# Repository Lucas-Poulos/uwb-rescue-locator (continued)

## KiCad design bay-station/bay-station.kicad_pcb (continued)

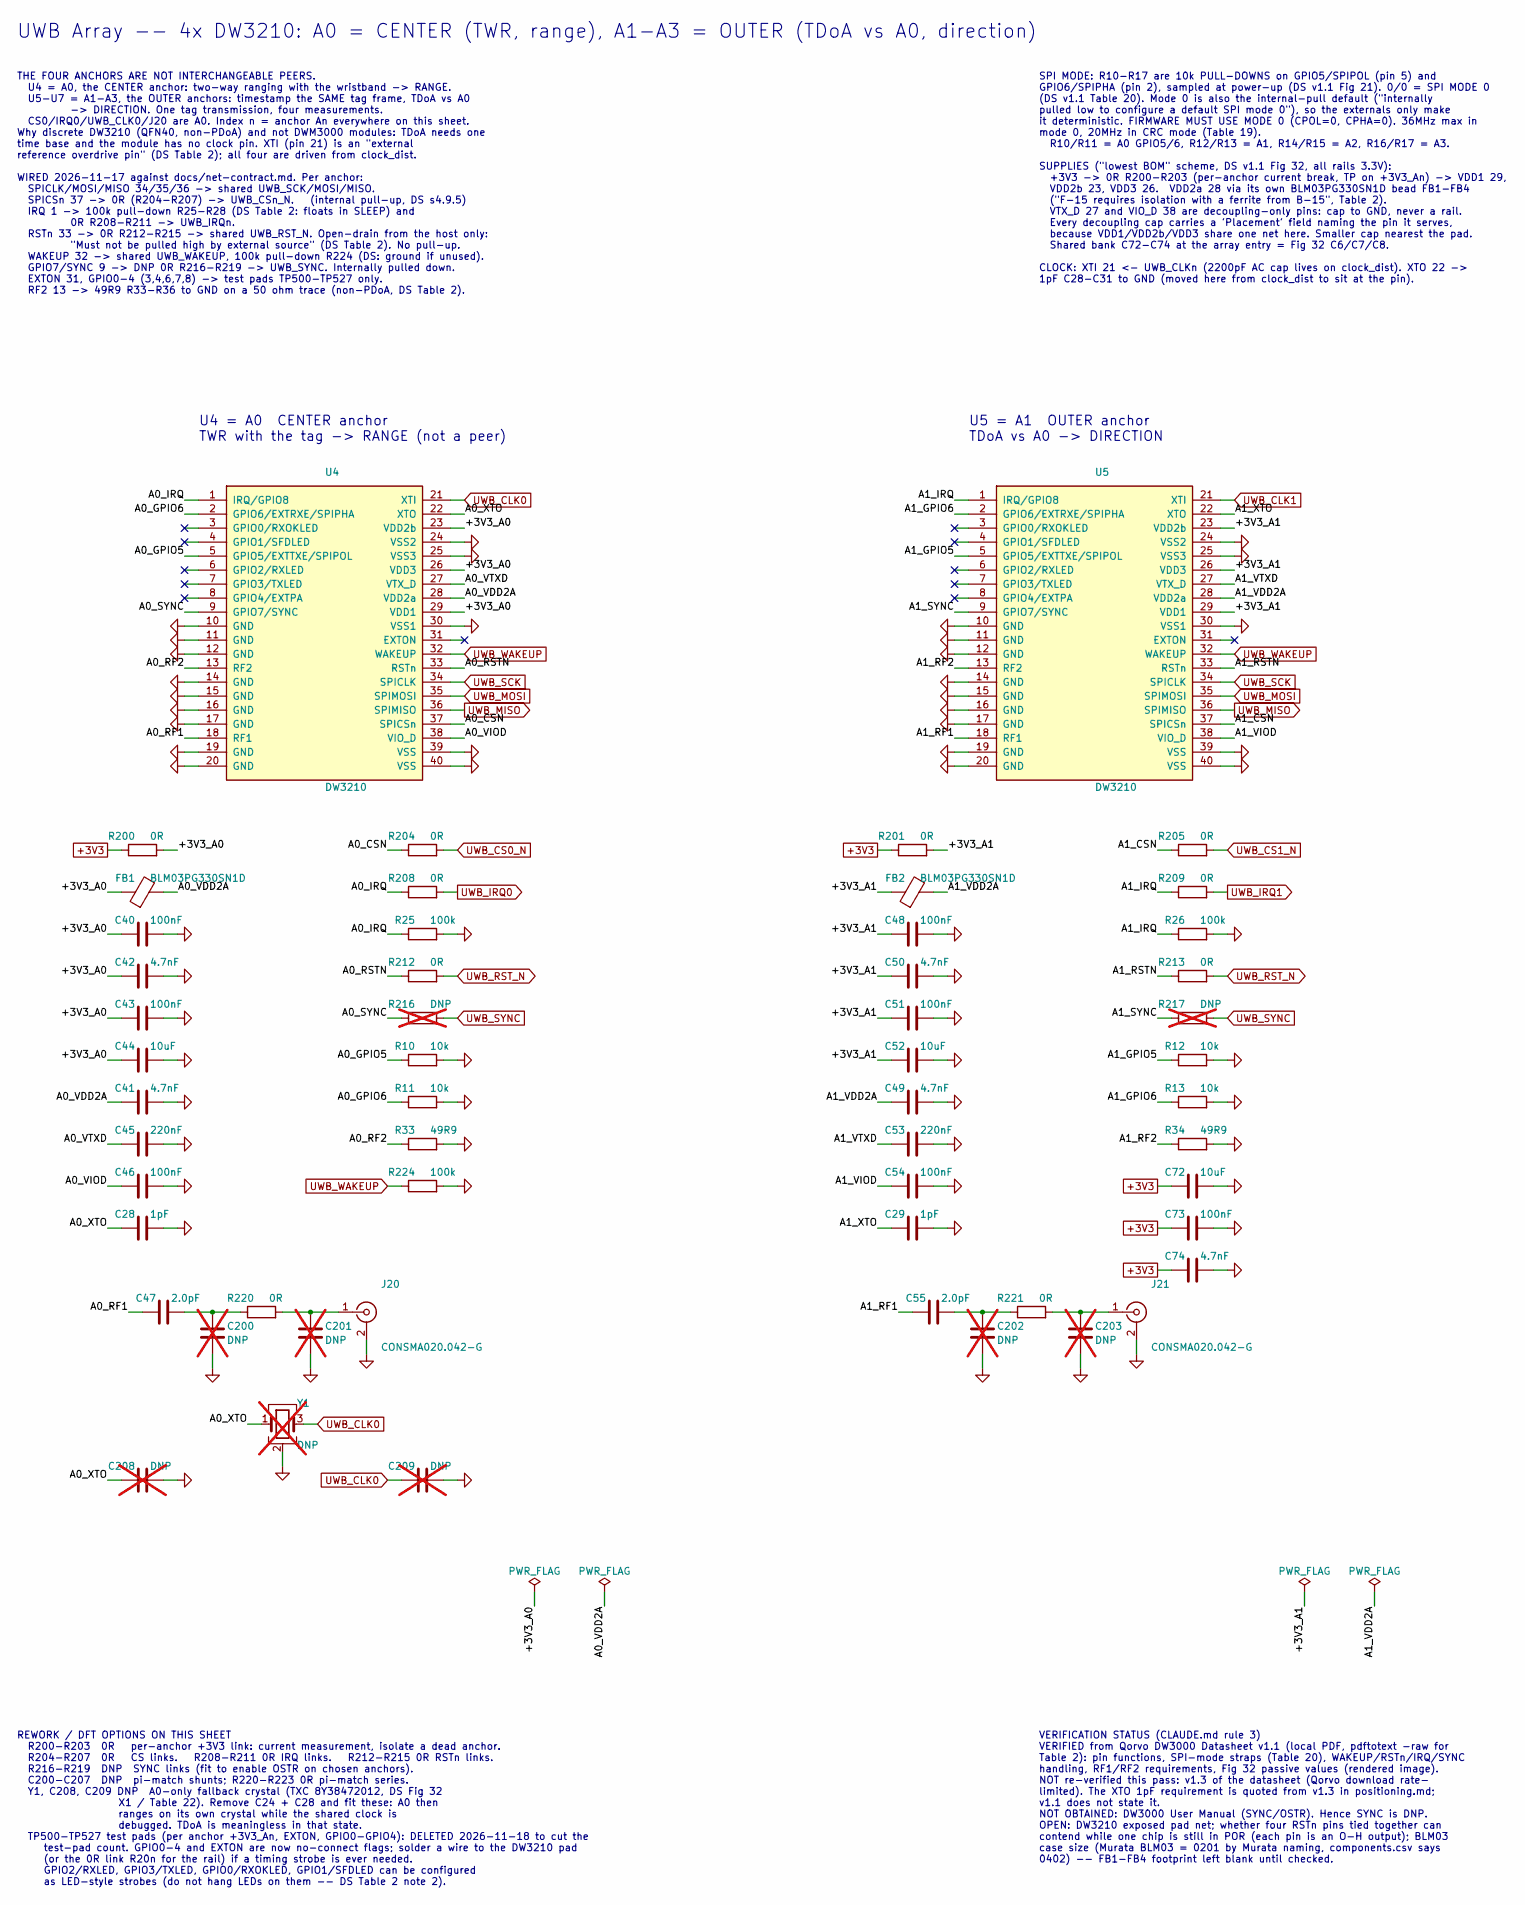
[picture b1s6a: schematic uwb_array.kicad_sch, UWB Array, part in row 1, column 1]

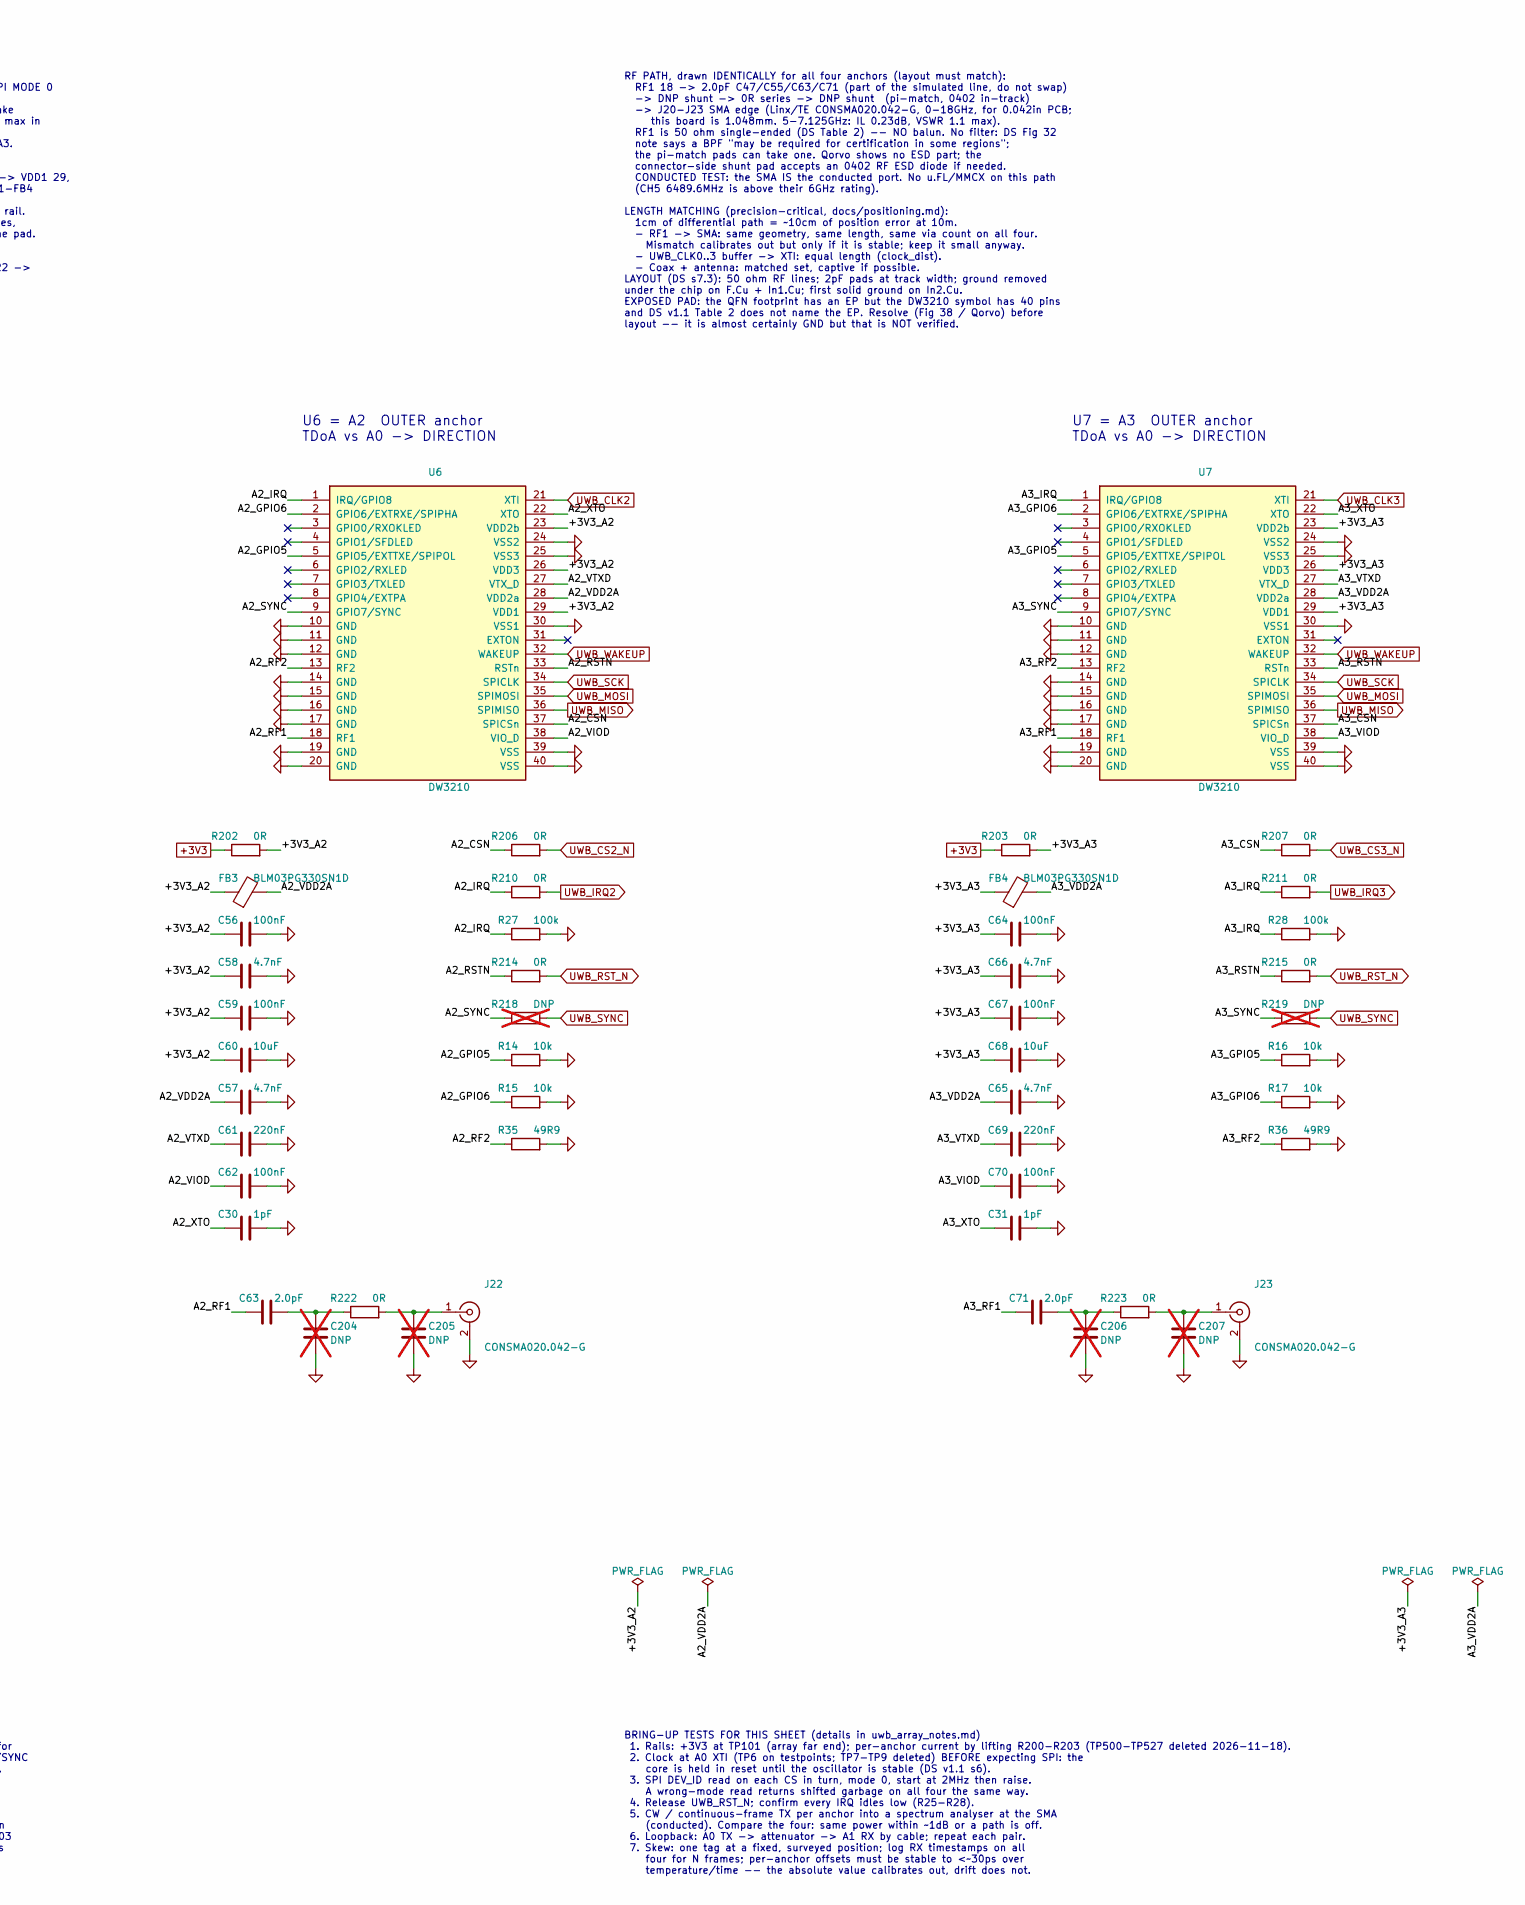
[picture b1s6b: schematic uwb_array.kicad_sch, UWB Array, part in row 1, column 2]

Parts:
C28, C29, C30, C31: 1pF; C_0402_1005Metric
C40, C43, C46, C48, C51, C54, C56, C59, C62, C64, C67, C70, C73: 100nF; C_0603_1608Metric
C41, C42, C49, C50, C57, C58, C65, C66, C74: 4.7nF; C_0603_1608Metric
C44, C52, C60, C68, C72: 10uF; C_0603_1608Metric
C45, C53, C61, C69: 220nF; C_0603_1608Metric
C47, C55, C63, C71: 2.0pF; C_0402_1005Metric
C200, C201, C202, C203, C204, C205, C206, C207, C208, C209: DNP; C_0402_1005Metric; not fitted
FB1, FB2, FB3, FB4: BLM03PG330SN1D; L_0201_0603Metric
J20, J21, J22, J23: CONSMA020.042-G; SMA_Linx_CONSMA020.042-G_EdgeMount_PLACEHOLDER
R10, R11, R12, R13, R14, R15, R16, R17: 10k; R_0603_1608Metric
R25, R26, R27, R28, R224: 100k; R_0603_1608Metric
R33, R34, R35, R36: 49R9; R_0402_1005Metric
R200, R201, R202, R203, R204, R205, R206, R207, R208, R209, R210, R211, R212, R213, R214, R215: 0R; R_0603_1608Metric
R216, R217, R218, R219: DNP; R_0603_1608Metric; not fitted
R220, R221, R222, R223: 0R; R_0402_1005Metric
U4, U5, U6, U7: DW3210; Qorvo_DW3210_QFN-40_5x5mm_P0.4mm_NoEP_PLACEHOLDER
Y1: DNP; Crystal_SMD_2016-4Pin_2.0x1.6mm; MPN 8Y38472012; not fitted

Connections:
+3V3: C72.1, C73.1, C74.1, R200.1, R201.1, R202.1, R203.1; also elsewhere on the board
/UWB Array/+3V3_A0: C40.1, C42.1, C43.1, C44.1, FB1.1, R200.2, U4.23 (VDD2b), U4.26 (VDD3), U4.29 (VDD1)
/UWB Array/+3V3_A1: C48.1, C50.1, C51.1, C52.1, FB2.1, R201.2, U5.23 (VDD2b), U5.26 (VDD3), U5.29 (VDD1)
/UWB Array/+3V3_A2: C56.1, C58.1, C59.1, C60.1, FB3.1, R202.2, U6.23 (VDD2b), U6.26 (VDD3), U6.29 (VDD1)
/UWB Array/+3V3_A3: C64.1, C66.1, C67.1, C68.1, FB4.1, R203.2, U7.23 (VDD2b), U7.26 (VDD3), U7.29 (VDD1)
/UWB Array/A0_CSN: R204.1, U4.37 (SPICSn)
/UWB Array/A0_GPIO5: R10.1, U4.5 (GPIO5/EXTTXE/SPIPOL)
/UWB Array/A0_GPIO6: R11.1, U4.2 (GPIO6/EXTRXE/SPIPHA)
/UWB Array/A0_IRQ: R25.1, R208.1, U4.1 (IRQ/GPIO8)
/UWB Array/A0_RF1: C47.1, U4.18 (RF1)
/UWB Array/A0_RF2: R33.1, U4.13 (RF2)
/UWB Array/A0_RSTN: R212.1, U4.33 (RSTn)
/UWB Array/A0_SYNC: R216.1, U4.9 (GPIO7/SYNC)
/UWB Array/A0_VDD2A: C41.1, FB1.2, U4.28 (VDD2a)
/UWB Array/A0_VIOD: C46.1, U4.38 (VIO_D)
/UWB Array/A0_VTXD: C45.1, U4.27 (VTX_D)
/UWB Array/A0_XTO: C28.1, C208.1, U4.22 (XTO), Y1.1
/UWB Array/A1_CSN: R205.1, U5.37 (SPICSn)
/UWB Array/A1_GPIO5: R12.1, U5.5 (GPIO5/EXTTXE/SPIPOL)
/UWB Array/A1_GPIO6: R13.1, U5.2 (GPIO6/EXTRXE/SPIPHA)
/UWB Array/A1_IRQ: R26.1, R209.1, U5.1 (IRQ/GPIO8)
/UWB Array/A1_RF1: C55.1, U5.18 (RF1)
/UWB Array/A1_RF2: R34.1, U5.13 (RF2)
/UWB Array/A1_RSTN: R213.1, U5.33 (RSTn)
/UWB Array/A1_SYNC: R217.1, U5.9 (GPIO7/SYNC)
/UWB Array/A1_VDD2A: C49.1, FB2.2, U5.28 (VDD2a)
/UWB Array/A1_VIOD: C54.1, U5.38 (VIO_D)
/UWB Array/A1_VTXD: C53.1, U5.27 (VTX_D)
/UWB Array/A1_XTO: C29.1, U5.22 (XTO)
/UWB Array/A2_CSN: R206.1, U6.37 (SPICSn)
/UWB Array/A2_GPIO5: R14.1, U6.5 (GPIO5/EXTTXE/SPIPOL)
/UWB Array/A2_GPIO6: R15.1, U6.2 (GPIO6/EXTRXE/SPIPHA)
/UWB Array/A2_IRQ: R27.1, R210.1, U6.1 (IRQ/GPIO8)
/UWB Array/A2_RF1: C63.1, U6.18 (RF1)
/UWB Array/A2_RF2: R35.1, U6.13 (RF2)
/UWB Array/A2_RSTN: R214.1, U6.33 (RSTn)
/UWB Array/A2_SYNC: R218.1, U6.9 (GPIO7/SYNC)
/UWB Array/A2_VDD2A: C57.1, FB3.2, U6.28 (VDD2a)
/UWB Array/A2_VIOD: C62.1, U6.38 (VIO_D)
/UWB Array/A2_VTXD: C61.1, U6.27 (VTX_D)
/UWB Array/A2_XTO: C30.1, U6.22 (XTO)
/UWB Array/A3_CSN: R207.1, U7.37 (SPICSn)
/UWB Array/A3_GPIO5: R16.1, U7.5 (GPIO5/EXTTXE/SPIPOL)
/UWB Array/A3_GPIO6: R17.1, U7.2 (GPIO6/EXTRXE/SPIPHA)
/UWB Array/A3_IRQ: R28.1, R211.1, U7.1 (IRQ/GPIO8)
/UWB Array/A3_RF1: C71.1, U7.18 (RF1)
/UWB Array/A3_RF2: R36.1, U7.13 (RF2)
/UWB Array/A3_RSTN: R215.1, U7.33 (RSTn)
/UWB Array/A3_SYNC: R219.1, U7.9 (GPIO7/SYNC)
/UWB Array/A3_VDD2A: C65.1, FB4.2, U7.28 (VDD2a)
/UWB Array/A3_VIOD: C70.1, U7.38 (VIO_D)
/UWB Array/A3_VTXD: C69.1, U7.27 (VTX_D)
/UWB Array/A3_XTO: C31.1, U7.22 (XTO)
GND: C28.2, C29.2, C30.2, C31.2, C40.2, C41.2, C42.2, C43.2, C44.2, C45.2, C46.2, C48.2, C49.2, C50.2, C51.2, C52.2, C53.2, C54.2, C56.2, C57.2, C58.2, C59.2, C60.2, C61.2, C62.2, C64.2, C65.2, C66.2, C67.2, C68.2, C69.2, C70.2, C72.2, C73.2, C74.2, C200.2, C201.2, C202.2, C203.2, C204.2, C205.2, C206.2, C207.2, C208.2, C209.2, J20.2 (Ext), J21.2 (Ext), J22.2 (Ext), J23.2 (Ext), R10.2, R11.2, R12.2, R13.2, R14.2, R15.2, R16.2, R17.2, R25.2, R26.2, R27.2, R28.2, R33.2, R34.2, R35.2, R36.2, R224.2, U4.10 (GND), U4.11 (GND), U4.12 (GND), U4.14 (GND), U4.15 (GND), U4.16 (GND), U4.17 (GND), U4.19 (GND), U4.20 (GND), U4.24 (VSS2), U4.25 (VSS3), U4.30 (VSS1), U4.39 (VSS), U4.40 (VSS), U5.10 (GND), U5.11 (GND), U5.12 (GND), U5.14 (GND), U5.15 (GND), U5.16 (GND), U5.17 (GND), U5.19 (GND), U5.20 (GND), U5.24 (VSS2), U5.25 (VSS3), U5.30 (VSS1), U5.39 (VSS), U5.40 (VSS), U6.10 (GND), U6.11 (GND), U6.12 (GND), U6.14 (GND), U6.15 (GND), U6.16 (GND), U6.17 (GND), U6.19 (GND), U6.20 (GND), U6.24 (VSS2), U6.25 (VSS3), U6.30 (VSS1), U6.39 (VSS), U6.40 (VSS), U7.10 (GND), U7.11 (GND), U7.12 (GND), U7.14 (GND), U7.15 (GND), U7.16 (GND), U7.17 (GND), U7.19 (GND), U7.20 (GND), U7.24 (VSS2), U7.25 (VSS3), U7.30 (VSS1), U7.39 (VSS), U7.40 (VSS), Y1.2 (G), Y1.4 (G); also elsewhere on the board
unnamed: C47.2, C200.1, R220.1
unnamed: C55.2, C202.1, R221.1
unnamed: C63.2, C204.1, R222.1
unnamed: C71.2, C206.1, R223.1
unnamed: C201.1, J20.1 (In), R220.2
unnamed: C203.1, J21.1 (In), R221.2
unnamed: C205.1, J22.1 (In), R222.2
unnamed: C207.1, J23.1 (In), R223.2
UWB_CLK0: C209.1, U4.21 (XTI), Y1.3; also elsewhere on the board
UWB_CLK1: U5.21 (XTI); also elsewhere on the board
UWB_CLK2: U6.21 (XTI); also elsewhere on the board
UWB_CLK3: U7.21 (XTI); also elsewhere on the board
UWB_CS0_N: R204.2; also elsewhere on the board
UWB_CS1_N: R205.2; also elsewhere on the board
UWB_CS2_N: R206.2; also elsewhere on the board
UWB_CS3_N: R207.2; also elsewhere on the board
UWB_IRQ0: R208.2; also elsewhere on the board
UWB_IRQ1: R209.2; also elsewhere on the board
UWB_IRQ2: R210.2; also elsewhere on the board
UWB_IRQ3: R211.2; also elsewhere on the board
UWB_MISO: U4.36 (SPIMISO), U5.36 (SPIMISO), U6.36 (SPIMISO), U7.36 (SPIMISO); also elsewhere on the board
UWB_MOSI: U4.35 (SPIMOSI), U5.35 (SPIMOSI), U6.35 (SPIMOSI), U7.35 (SPIMOSI); also elsewhere on the board
UWB_RST_N: R212.2, R213.2, R214.2, R215.2; also elsewhere on the board
UWB_SCK: U4.34 (SPICLK), U5.34 (SPICLK), U6.34 (SPICLK), U7.34 (SPICLK); also elsewhere on the board
UWB_SYNC: R216.2, R217.2, R218.2, R219.2; also elsewhere on the board
UWB_WAKEUP: R224.1, U4.32 (WAKEUP), U5.32 (WAKEUP), U6.32 (WAKEUP), U7.32 (WAKEUP); also elsewhere on the board

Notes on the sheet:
VERIFICATION STATUS (CLAUDE.md rule 3) VERIFIED from Qorvo DW3000 Datasheet v1.1 (local PDF, pdftotext -raw for Table 2): pin functions, SPI-mode straps (Table 20), WAKEUP/RSTn/IRQ/SYNC handling, RF1/RF2 requirements, Fig 32 passive values (rendered image). NOT re-verified this pass: v1.3 of the da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
U7 = A3 OUTER anchor TDoA vs A0 -> DIRECTION
U6 = A2 OUTER anchor TDoA vs A0 -> DIRECTION
BRING-UP TESTS FOR THIS SHEET (details in uwb_array_notes.md) 1. Rails: +3V3 at TP101 (array far end); per-anchor current by lifting R200-R203 (TP500-TP527 deleted 2026-11-18). 2. Clock at A0 XTI (TP6 on testpoints; TP7-TP9 deleted) BEFORE expecting SPI: the core is held in reset until the oscillat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
UWB Array -- 4x DW3210: A0 = CENTER (TWR, range), A1-A3 = OUTER (TDoA vs A0, direction)
THE FOUR ANCHORS ARE NOT INTERCHANGEABLE PEERS. U4 = A0, the CENTER anchor: two-way ranging with the wristband -> RANGE. U5-U7 = A1-A3, the OUTER anchors: timestamp the SAME tag frame, TDoA vs A0 -> DIRECTION. One tag transmission, four measurements. CS0/IRQ0/UWB_CLK0/J20 are A0. Index n = anchor A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
SPI MODE: R10-R17 are 10k PULL-DOWNS on GPIO5/SPIPOL (pin 5) and GPIO6/SPIPHA (pin 2), sampled at power-up (DS v1.1 Fig 21). 0/0 = SPI MODE 0 (DS v1.1 Table 20). Mode 0 is also the internal-pull default ("internally pulled low to configure a default SPI mode 0"), so the externals only make it deter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
RF PATH, drawn IDENTICALLY for all four anchors (layout must match): RF1 18 -> 2.0pF C47/C55/C63/C71 (part of the simulated line, do not swap) -> DNP shunt -> 0R series -> DNP shunt (pi-match, 0402 in-track) -> J20-J23 SMA edge (Linx/TE CONSMA020.042-G, 0-18GHz, for 0.042in PCB; this board is 1.048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
U5 = A1 OUTER anchor TDoA vs A0 -> DIRECTION
U4 = A0 CENTER anchor TWR with the tag -> RANGE (not a peer)
REWORK / DFT OPTIONS ON THIS SHEET R200-R203 0R per-anchor +3V3 link: current measurement, isolate a dead anchor. R204-R207 0R CS links. R208-R211 0R IRQ links. R212-R215 0R RSTn links. R216-R219 DNP SYNC links (fit to enable OSTR on chosen anchors). C200-C207 DNP pi-match shunts; R220-R223 0R pi-m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

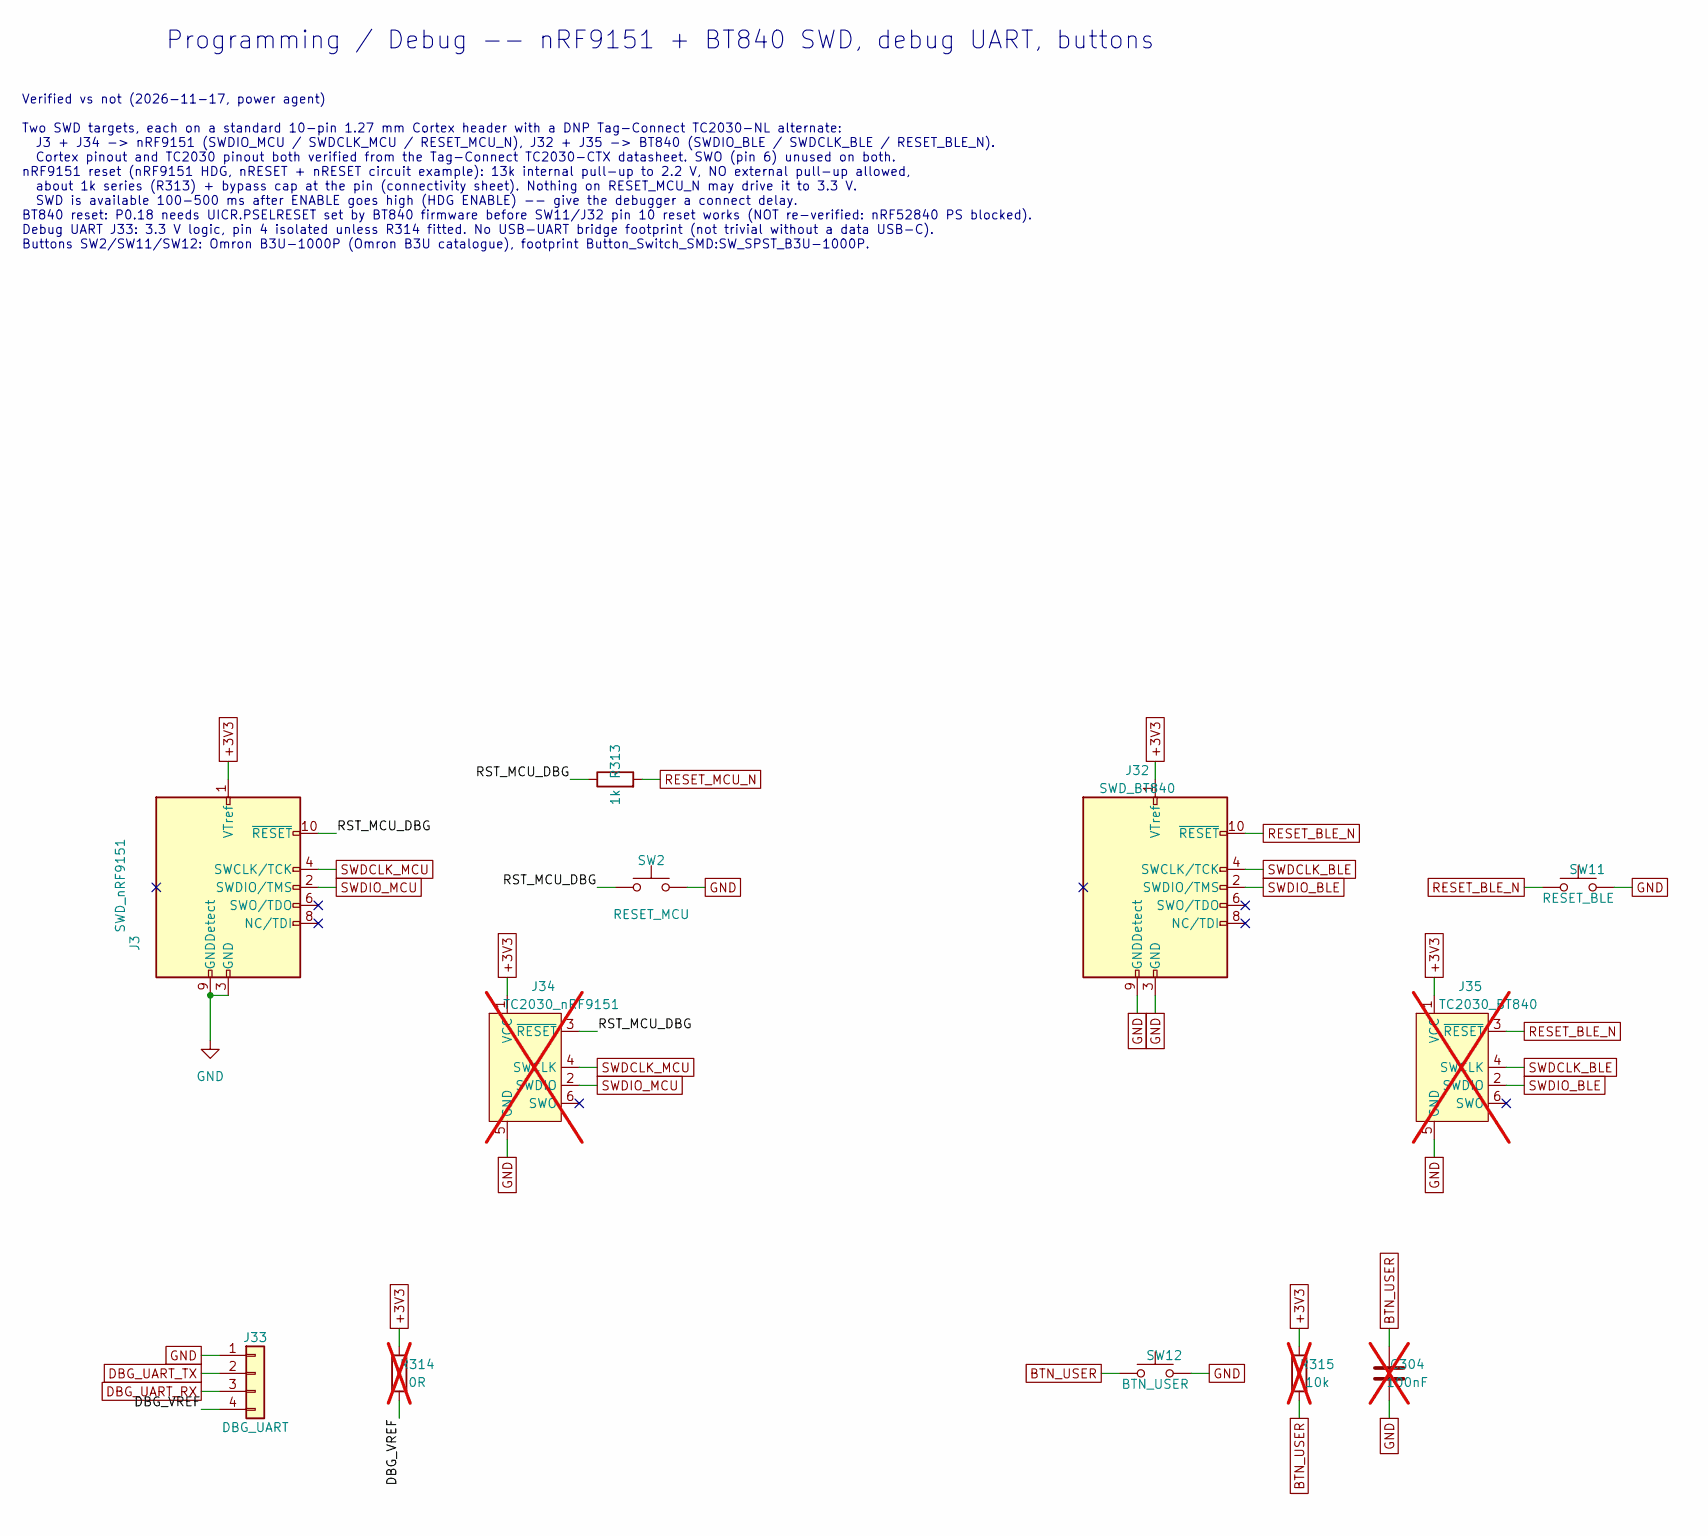
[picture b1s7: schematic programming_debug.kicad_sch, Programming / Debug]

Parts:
C304: 100nF; C_0603_1608Metric; not fitted
J3: SWD_nRF9151; PinHeader_2x05_P1.27mm_Vertical
J32: SWD_BT840; PinHeader_2x05_P1.27mm_Vertical
J33: DBG_UART; PinHeader_1x04_P2.54mm_Vertical
J34: TC2030_nRF9151; Tag-Connect_TC2030-IDC-NL_2x03_P1.27mm_Vertical; not fitted
J35: TC2030_BT840; Tag-Connect_TC2030-IDC-NL_2x03_P1.27mm_Vertical; not fitted
R313: 1k; R_0603_1608Metric
R314: 0R; R_0603_1608Metric; not fitted
R315: 10k; R_0603_1608Metric; not fitted
SW2: RESET_MCU; SW_SPST_B3U-1000P; MPN B3U-1000P
SW11: RESET_BLE; SW_SPST_B3U-1000P; MPN B3U-1000P
SW12: BTN_USER; SW_SPST_B3U-1000P; MPN B3U-1000P

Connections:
+3V3: J3.1 (VTref), J32.1 (VTref), J34.1 (VCC), J35.1 (VCC), R314.1, R315.1; also elsewhere on the board
/Programming / Debug/DBG_VREF: J33.4, R314.2
/Programming / Debug/RST_MCU_DBG: J3.10 (~RESET), J34.3 (~RESET), R313.1, SW2.1
BTN_USER: C304.1, R315.2, SW12.1; also elsewhere on the board
DBG_UART_RX: J33.3; also elsewhere on the board
DBG_UART_TX: J33.2; also elsewhere on the board
GND: C304.2, J3.3 (GND), J3.5 (GND), J3.9 (GNDDetect), J32.3 (GND), J32.5 (GND), J32.9 (GNDDetect), J33.1, J34.5 (GND), J35.5 (GND), SW2.2, SW11.2, SW12.2; also elsewhere on the board
RESET_BLE_N: J32.10 (~RESET), J35.3 (~RESET), SW11.1; also elsewhere on the board
RESET_MCU_N: R313.2; also elsewhere on the board
SWDCLK_BLE: J32.4 (SWCLK/TCK), J35.4 (SWCLK); also elsewhere on the board
SWDCLK_MCU: J3.4 (SWCLK/TCK), J34.4 (SWCLK); also elsewhere on the board
SWDIO_BLE: J32.2 (SWDIO/TMS), J35.2 (SWDIO); also elsewhere on the board
SWDIO_MCU: J3.2 (SWDIO/TMS), J34.2 (SWDIO); also elsewhere on the board

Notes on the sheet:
Verified vs not (2026-11-17, power agent) Two SWD targets, each on a standard 10-pin 1.27 mm Cortex header with a DNP Tag-Connect TC2030-NL alternate: J3 + J34 -> nRF9151 (SWDIO_MCU / SWDCLK_MCU / RESET_MCU_N), J32 + J35 -> BT840 (SWDIO_BLE / SWDCLK_BLE / RESET_BLE_N). Cortex pinout and TC2030 pino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
Programming / Debug -- nRF9151 + BT840 SWD, debug UART, buttons

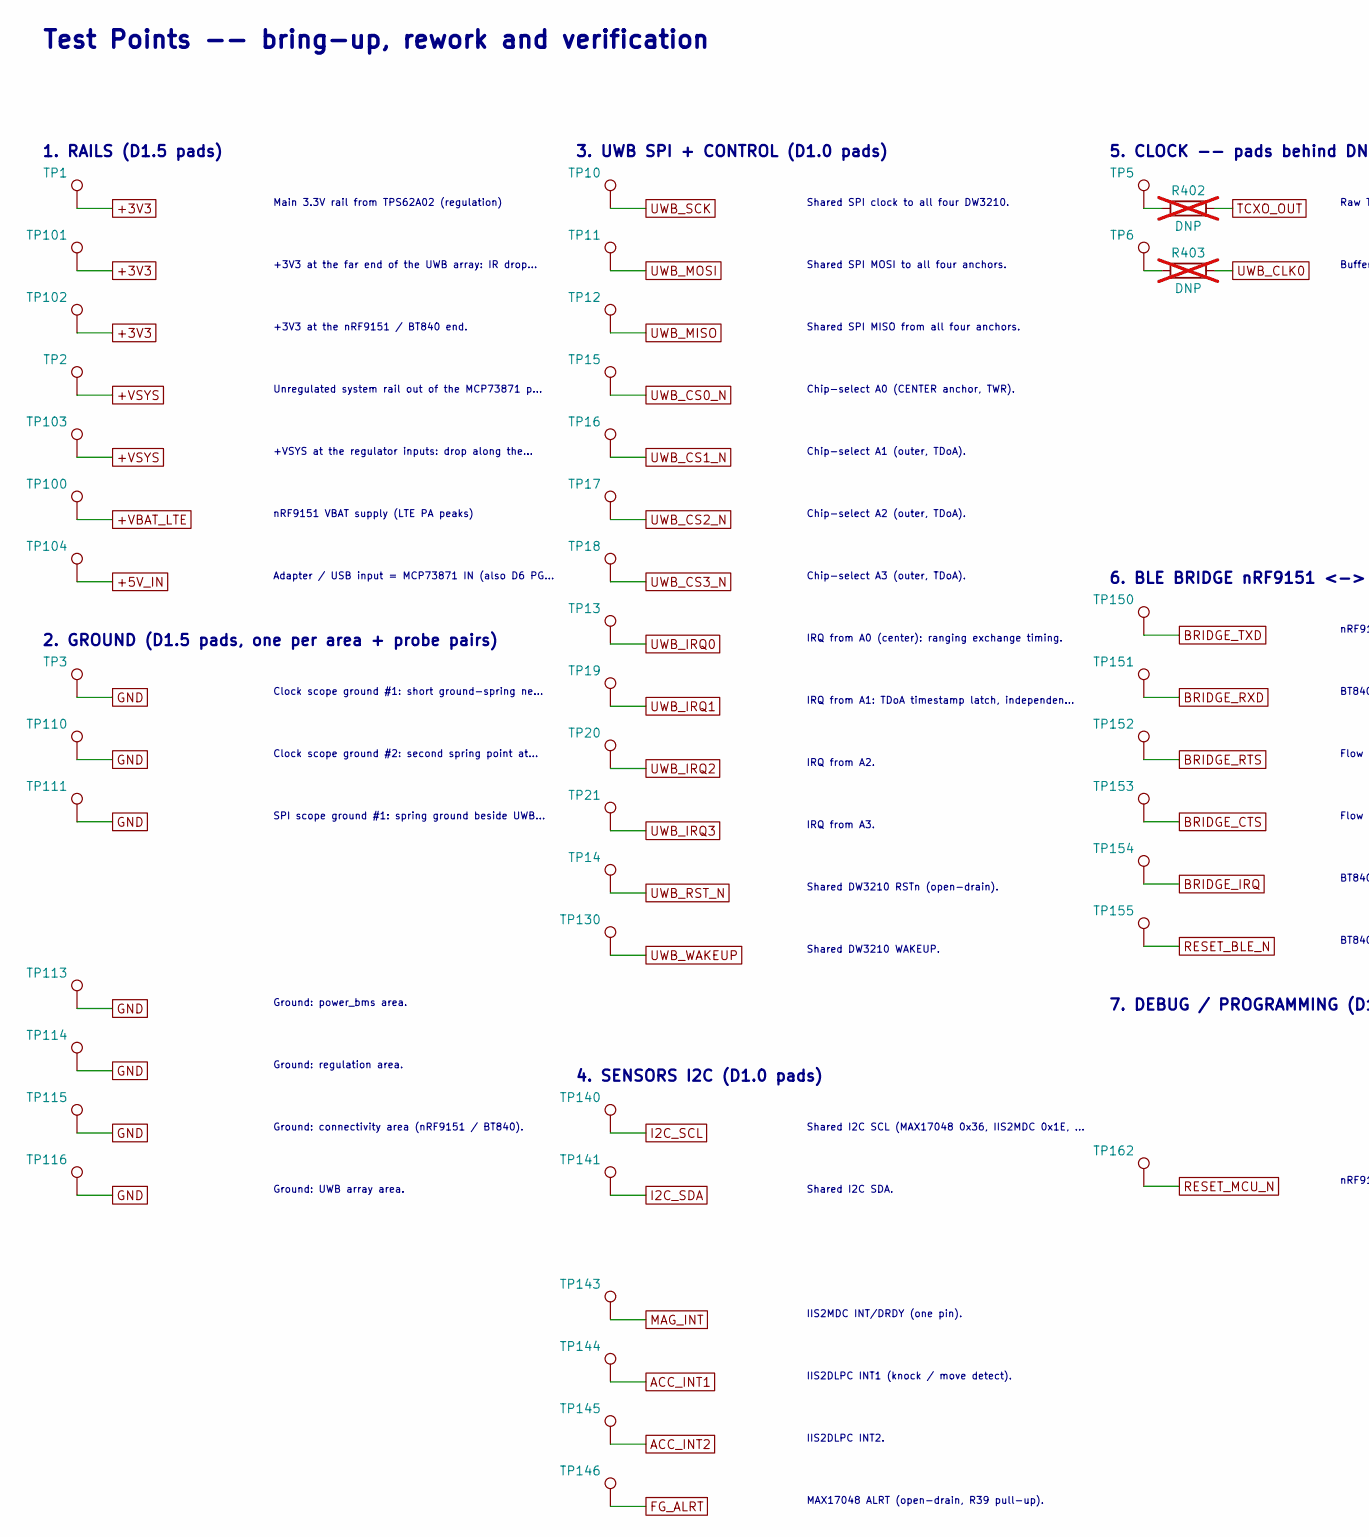
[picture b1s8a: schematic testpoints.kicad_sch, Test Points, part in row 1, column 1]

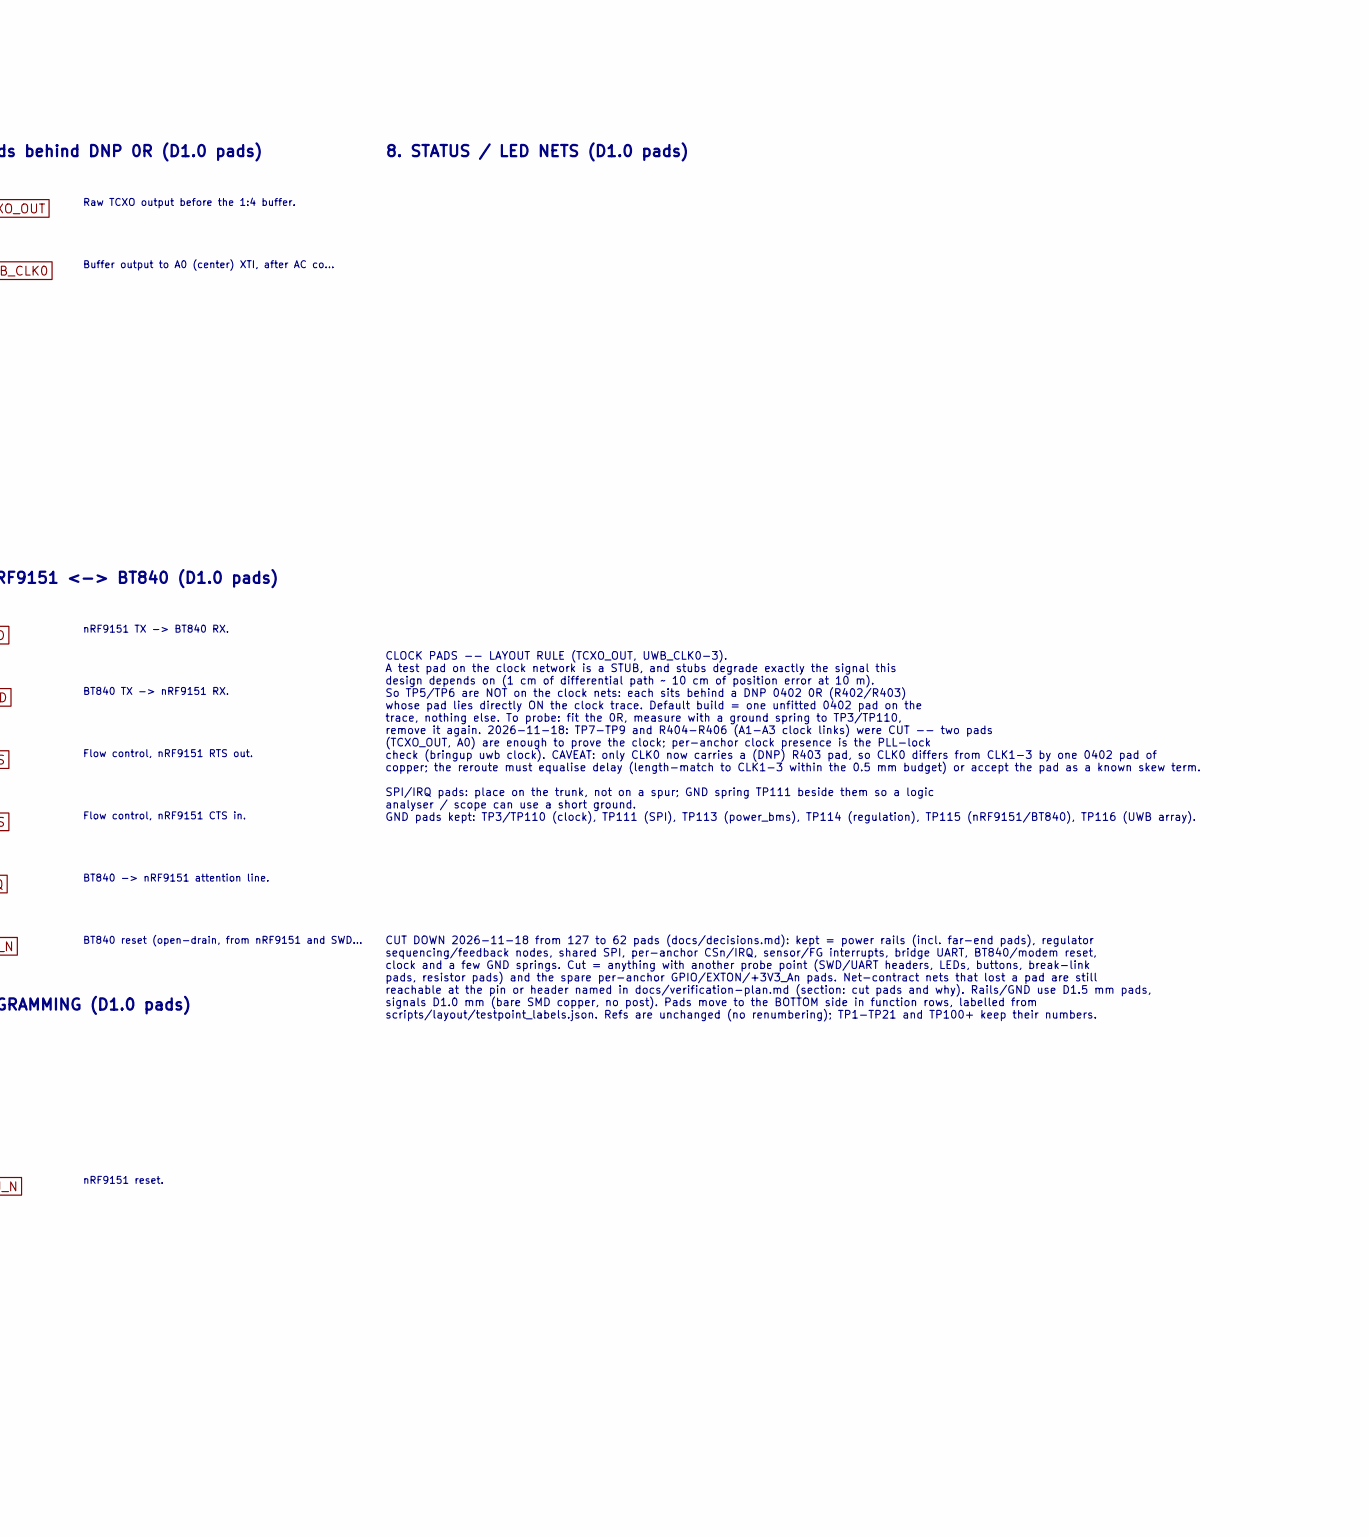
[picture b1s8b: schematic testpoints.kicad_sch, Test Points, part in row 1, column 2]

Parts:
R402, R403: DNP; R_0402_1005Metric; not fitted
TP1, TP101, TP102: +3V3; TestPoint_Pad_D1.5mm
TP2, TP103: +VSYS; TestPoint_Pad_D1.5mm
TP3, TP110, TP111, TP113, TP114, TP115, TP116: GND; TestPoint_Pad_D1.5mm
TP5: TCXO_OUT; TestPoint_Pad_D1.0mm
TP6: UWB_CLK0; TestPoint_Pad_D1.0mm
TP10: UWB_SCK; TestPoint_Pad_D1.0mm
TP11: UWB_MOSI; TestPoint_Pad_D1.0mm
TP12: UWB_MISO; TestPoint_Pad_D1.0mm
TP13: UWB_IRQ0; TestPoint_Pad_D1.0mm
TP14: UWB_RST_N; TestPoint_Pad_D1.0mm
TP15: UWB_CS0_N; TestPoint_Pad_D1.0mm
TP16: UWB_CS1_N; TestPoint_Pad_D1.0mm
TP17: UWB_CS2_N; TestPoint_Pad_D1.0mm
TP18: UWB_CS3_N; TestPoint_Pad_D1.0mm
TP19: UWB_IRQ1; TestPoint_Pad_D1.0mm
TP20: UWB_IRQ2; TestPoint_Pad_D1.0mm
TP21: UWB_IRQ3; TestPoint_Pad_D1.0mm
TP100: +VBAT_LTE; TestPoint_Pad_D1.5mm
TP104: +5V_IN; TestPoint_Pad_D1.5mm
TP130: UWB_WAKEUP; TestPoint_Pad_D1.0mm
TP140: I2C_SCL; TestPoint_Pad_D1.0mm
TP141: I2C_SDA; TestPoint_Pad_D1.0mm
TP143: MAG_INT; TestPoint_Pad_D1.0mm
TP144: ACC_INT1; TestPoint_Pad_D1.0mm
TP145: ACC_INT2; TestPoint_Pad_D1.0mm
TP146: FG_ALRT; TestPoint_Pad_D1.0mm
TP150: BRIDGE_TXD; TestPoint_Pad_D1.0mm
TP151: BRIDGE_RXD; TestPoint_Pad_D1.0mm
TP152: BRIDGE_RTS; TestPoint_Pad_D1.0mm
TP153: BRIDGE_CTS; TestPoint_Pad_D1.0mm
TP154: BRIDGE_IRQ; TestPoint_Pad_D1.0mm
TP155: RESET_BLE_N; TestPoint_Pad_D1.0mm
TP162: RESET_MCU_N; TestPoint_Pad_D1.0mm

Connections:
+3V3: TP1.1 (1_1), TP101.1 (1_1), TP102.1 (1_1); also elsewhere on the board
+5V_IN: TP104.1 (1_1); also elsewhere on the board
+VBAT_LTE: TP100.1 (1_1); also elsewhere on the board
+VSYS: TP2.1 (1_1), TP103.1 (1_1); also elsewhere on the board
ACC_INT1: TP144.1 (1_1); also elsewhere on the board
ACC_INT2: TP145.1 (1_1); also elsewhere on the board
BRIDGE_CTS: TP153.1 (1_1); also elsewhere on the board
BRIDGE_IRQ: TP154.1 (1_1); also elsewhere on the board
BRIDGE_RTS: TP152.1 (1_1); also elsewhere on the board
BRIDGE_RXD: TP151.1 (1_1); also elsewhere on the board
BRIDGE_TXD: TP150.1 (1_1); also elsewhere on the board
FG_ALRT: TP146.1 (1_1); also elsewhere on the board
GND: TP3.1 (1_1), TP110.1 (1_1), TP111.1 (1_1), TP113.1 (1_1), TP114.1 (1_1), TP115.1 (1_1), TP116.1 (1_1); also elsewhere on the board
I2C_SCL: TP140.1 (1_1); also elsewhere on the board
I2C_SDA: TP141.1 (1_1); also elsewhere on the board
MAG_INT: TP143.1 (1_1); also elsewhere on the board
unnamed: R402.1, TP5.1 (1_1)
unnamed: R403.1, TP6.1 (1_1)
RESET_BLE_N: TP155.1 (1_1); also elsewhere on the board
RESET_MCU_N: TP162.1 (1_1); also elsewhere on the board
TCXO_OUT: R402.2; also elsewhere on the board
UWB_CLK0: R403.2; also elsewhere on the board
UWB_CS0_N: TP15.1 (1_1); also elsewhere on the board
UWB_CS1_N: TP16.1 (1_1); also elsewhere on the board
UWB_CS2_N: TP17.1 (1_1); also elsewhere on the board
UWB_CS3_N: TP18.1 (1_1); also elsewhere on the board
UWB_IRQ0: TP13.1 (1_1); also elsewhere on the board
UWB_IRQ1: TP19.1 (1_1); also elsewhere on the board
UWB_IRQ2: TP20.1 (1_1); also elsewhere on the board
UWB_IRQ3: TP21.1 (1_1); also elsewhere on the board
UWB_MISO: TP12.1 (1_1); also elsewhere on the board
UWB_MOSI: TP11.1 (1_1); also elsewhere on the board
UWB_RST_N: TP14.1 (1_1); also elsewhere on the board
UWB_SCK: TP10.1 (1_1); also elsewhere on the board
UWB_WAKEUP: TP130.1 (1_1); also elsewhere on the board

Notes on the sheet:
Shared SPI clock to all four DW3210.
Adapter / USB input = MCP73871 IN (also D6 PG...
IIS2DLPC INT2.
8. STATUS / LED NETS (D1.0 pads)
IRQ from A1: TDoA timestamp latch, independen...
CUT DOWN 2026-11-18 from 127 to 62 pads (docs/decisions.md): kept = power rails (incl. far-end pads), regulator sequencing/feedback nodes, shared SPI, per-anchor CSn/IRQ, sensor/FG interrupts, bridge UART, BT840/modem reset, clock and a few GND springs. Cut = anything with another probe point (SWD/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
Chip-select A0 (CENTER anchor, TWR).
Test Points -- bring-up, rework and verification
+3V3 at the nRF9151 / BT840 end.
nRF9151 reset.
Flow control, nRF9151 CTS in.
IRQ from A2.
Ground: regulation area.
IIS2DLPC INT1 (knock / move detect).
Raw TCXO output before the 1:4 buffer.
Shared SPI MOSI to all four anchors.
+3V3 at the far end of the UWB array: IR drop...
6. BLE BRIDGE nRF9151 <-> BT840 (D1.0 pads)
Chip-select A2 (outer, TDoA).
Ground: power_bms area.
+VSYS at the regulator inputs: drop along the...
IIS2MDC INT/DRDY (one pin).
BT840 TX -> nRF9151 RX.
Clock scope ground #2: second spring point at...
Main 3.3V rail from TPS62A02 (regulation)
7. DEBUG / PROGRAMMING (D1.0 pads)
Shared SPI MISO from all four anchors.
Buffer output to A0 (center) XTI, after AC co...
CLOCK PADS -- LAYOUT RULE (TCXO_OUT, UWB_CLK0-3). A test pad on the clock network is a STUB, and stubs degrade exactly the signal this design depends on (1 cm of differential path ~ 10 cm of position error at 10 m). So TP5/TP6 are NOT on the clock nets: each sits behind a DNP 0402 0R (R402/R403) wh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
2. GROUND (D1.5 pads, one per area + probe pairs)
Ground: UWB array area.
Unregulated system rail out of the MCP73871 p...
Flow control, nRF9151 RTS out.
SPI scope ground #1: spring ground beside UWB...
3. UWB SPI + CONTROL (D1.0 pads)
IRQ from A3.
Shared I2C SDA.
BT840 -> nRF9151 attention line.
Clock scope ground #1: short ground-spring ne...
Shared I2C SCL (MAX17048 0x36, IIS2MDC 0x1E, ...

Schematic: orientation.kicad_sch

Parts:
C35, C36, C402, C404: 100nF; C_0603_1608Metric
C400: 220nF; C_0603_1608Metric
C401, C403: 10uF; C_0603_1608Metric
R407, R408, R409, R410, R411, R414: 0R; R_0603_1608Metric
R415: DNP; R_0603_1608Metric; not fitted
TP121: +3V3_SNS; TestPoint_Pad_D1.5mm
U10: IIS2MDC; LGA-12_2x2mm_P0.5mm
U11: IIS2DLPC; LGA-12_2x2mm_P0.5mm

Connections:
+3V3: R411.1; also elsewhere on the board
/Orientation/+3V3_SNS: C35.1, C36.1, C401.1, C402.1, C403.1, C404.1, R411.2, R414.1, TP121.1 (1_1), U10.3 (~CS), U10.9 (Vdd), U10.10 (Vdd_IO), U11.2 (~CS), U11.9 (Vdd), U11.10 (Vdd_IO)
/Orientation/U10_C1: C400.1, U10.5 (C1)
/Orientation/U10_SCL: R407.2, U10.1 (SCL/SPC)
/Orientation/U10_SDA: R408.2, U10.4 (SDA/SDI/SDO)
/Orientation/U11_SA0: R414.2, R415.1, U11.3 (SDO/SA0)
/Orientation/U11_SCL: R409.2, U11.1 (SCL/SPC)
/Orientation/U11_SDA: R410.2, U11.4 (SDA/SDI/SDO)
ACC_INT1: U11.12 (INT1); also elsewhere on the board
ACC_INT2: U11.11 (INT2); also elsewhere on the board
GND: C35.2, C36.2, C400.2, C401.2, C402.2, C403.2, C404.2, R415.2, U10.6 (GND), U10.8 (GND), U11.6 (GND), U11.7 (RES), U11.8 (GND); also elsewhere on the board
I2C_SCL: R407.1, R409.1; also elsewhere on the board
I2C_SDA: R408.1, R410.1; also elsewhere on the board
MAG_INT: U10.7 (INT/DRDY); also elsewhere on the board

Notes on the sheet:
I2C BUS (shared with MAX17048 on power_bms; pull-ups R37/R38 3.3k on connectivity): MAX17048 0x36 fixed (19-6171 Rev 7, "Slave Address": 0110110b) IIS2MDC 0x1E fixed (DocID030986 Rev 1 Table 21, default address 0011110b; no address pin) IIS2DLPC 0x19 SA0 = VddIO (DocID031788 Rev 4: SAD 001100xb, SA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
Address straps (fitted / DNP alternate)
Sensor rail break + test pad
VERIFIED vs NOT. Verified from the real PDFs (pdftotext -raw and -layout): pinouts (IIS2MDC Table 2 -- identical to the LIS2MDL Table 2 and to the KiCad stock LIS2MDL symbol; IIS2DLPC Table 2), I2C addresses, CS/SA0 rules, C1 = 220nF low ESR, decoupling values, supply ranges. Copies read: IIS2MDC D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
Decoupling (values from ST)
Per-device I2C isolation (0R)
Orientation -- heading (IIS2MDC) + tilt (IIS2DLPC)
WHY THIS SHEET EXISTS. The UWB array reports a tag RELATIVE to its own antenna frame. Georeferencing needs WHERE the station is (GNSS) and WHICH WAY it faces (heading). GNSS now comes from the nRF9151 on the connectivity sheet (MAX-M10S U9 removed 2026-11-17, with its C32/C33/C34, which decoupled o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
MAGNETOMETER LAYOUT KEEP-OUT (U10) -- this decides heading accuracy, not the part. ST: "Keep currents higher than 10 mA a few millimeters away from the sensor IC" (IIS2MDC DocID030986 Rev 1 sec 5.2). This board has three much bigger sources: 1. BUCK INDUCTOR (TPS62A02 L1, regulation sheet): switchi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

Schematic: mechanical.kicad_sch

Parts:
FID1, FID2, FID3: Fiducial; Fiducial_1mm_Mask2mm
H1, H2, H3, H4: MountingHole; MountingHole_3.2mm_M3

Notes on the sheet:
GROUNDING THE MOUNTING HOLES -- recommendation, not yet applied. H1-H4 are Mechanical:MountingHole + MountingHole_3.2mm_M3: NPTH, no pad, no net. Recommend converting them to MountingHole_Pad + MountingHole_3.2mm_M3_Pad_Via tied to GND, because: - ESD: the station is handled outdoors and its SMA/co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
Three global fiducials, top side (all SMD parts are top side today). Place non-collinear at three corners (an L, not a line) so the pick-and-place camera can solve rotation AND skew. Asymmetric placement also stops a board being loaded 180 deg rotated. If parts are ever put on B.Cu, add FID4-FID6 o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
Mechanical -- 4x M3 mounting holes (H1-H4), 3 fiducials (FID1-FID3)
Fiducials -- 3 global (FID1-FID3)
Generic M3-clearance mounting holes (Mechanical:MountingHole, no electrical connection), placeholder positions only. Anchor placement and enclosure geometry are still an open decision -- see docs/decisions.md, 'Anchor placement / enclosure for the bay station's 4 UWB anchors'. Final hole positions 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
